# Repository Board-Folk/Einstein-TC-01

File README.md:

# Einstein TC-01

Repository for the 2025 Board Folk recreation of the main board of the Einstein TC-01 computer from Tatung.

This repository contains the Bill-of-Materials (iBOM), Gerbers and Kicad files for a remake of the Tatung Einstein TC-01 main board.

Projects are in Kicad 9.

## Revisions

* Version 1.1 Initial Public Release

## Modifications

* The 3 digit references have been abridged so they work in Kicad
* The factory modifications (cuts and bodge wires) for the reset circuit have been included on the board
* Bodge capacitor C70 included on board for printer port strobe delay
* A solder jumper next to socket M16 provides the common modification of 5V power to pin 6 on the video output socket as you'd have on a BBC Micro
* Some small silkscreen improvements have been made to avoid confusion

## Build Notes

* Power connectors are 5.08mm pin headers
* M6 keyboard pin header is 2.5mm not 2.54mm pitch
* Corner line indicator on transistor footprints signifies flat front side direction, NOT pin 1
* BC307 can be subtituted for BC557
* BC308 can be subtituted for BC558
* Reset switch is the same as the one found on the TRS-80 Model I
* The ADC0844 alternative footprint is a µPD7002 which requires C13 populating with 33nF (untested)
* The value/range of L101 "Chrominance Rejector" is at this time unknown

## Archive

Currently contains the original copy of the v1.1 main board, which hasn't changed. The updated main Kicad folder now contains additional symbols and footprints only.

## Credit

Mainboard PCB layout by Rob Taylor @peepouk. Schematics recreated by Ian Cudlip @grandoldian.

## Expansions

### TMSAdapterTC01

Adapter board to allow the use of a TMS9929 chip on the Tatung Einstein TC-01.

### EinsteinTC01PS2

Arduino Nano based PS/2 Keyboard Adapter for the TC-01.

### EinsteinTC01PS2Mini

ATMEGA328 based PS/2 Keyboard Adapter for the TC-01.

### V9958AdapterTC01

Yamaha V9958/V9938 Adapter with 192K Video RAM for the TC-01.

### TC02Mini

Simple non-replica remake of the TC-02 80 column adapter for the TC01.

### Joystick Adapters

#### TC01AtariJoystick

Dual Atari Digital Joystick Adapter.

#### Withdrawn Tandy Joystick Adapter

It turns out the y axis on Tandy joysticks is connected the other way round, which means it will require circuitry to make it work for Einstein games. Trying to think of something clever for that.

## Remixes

### Einstein CE

Simplified Einstein with bits removed to fit on a small board. See description in folder.

## Coming Soon

* Another, comprehensive remix with expansions

## Links

   [10.6875MHz HC-49U Crystal](https://slawmir.com.pl/rezonator-10-6875mhz-hc49u-x5-p-6105.html)  
   [5 pin "Domino" DIN Socket for Serial Port](https://vintage.imitation.parts/products/bbc-micro-parts/din-5-pcb-socket)  
   [Modifyable bracket for holding standard Volume Pot](https://sonicsynths.com/products/pcb_mounting_bracket_for_16mm_commercial_grade_pots)

## Thanks

  * The rest of the Board Folk Team

## Legal

As the product of this project is a replica of a proprietary product, the the author makes no claim of copyright to the schematics nor PCB layouts and releases these into the public domain, solely for the purposes of study and historical preservation.

You are free to produce PCBs based on this project's designs at your own risk and without limitation, for your own use or for sale and/or repair at a reasonable price. Attribution is appreciated. The authors are not obliged to provide support of any kind. 

Under no circumstances will the authors be held responsible or liable in any way for losses, damages or costs resulting from the use of the information and/or resources of this project. 

The resources are provided "as-is" without warranty of any kind, either expressed or implied, including, but not limited to, the implied warranties of merchantability and fitness for a particular purpose.

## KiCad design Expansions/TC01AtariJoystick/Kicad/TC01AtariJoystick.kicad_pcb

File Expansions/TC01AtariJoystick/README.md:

# Einstein TC01 Dual Atari Digital Joystick Adapter v1.1

Dual joystick adapter for Atari and compatible (Kempston/C64/Amiga/ST etc) digital joysticks. Tested with SVI Quickshot II Plus.

Based on Wizard Development 'BBC' joystick interface. Very clever, many thanks.

Update: Turns out having a fixed resistor at R1 was a bad idea as the output of the Vref circuit seems to be different between main board builds. This makes the analogue centre different. You can patch in a variable resistor/pot as an adjustment. One board needed changing to ~1K. Will post an update soon and some BASIC code for adjustment/tweaking.

## Versions

v1.1 Fix for x direction

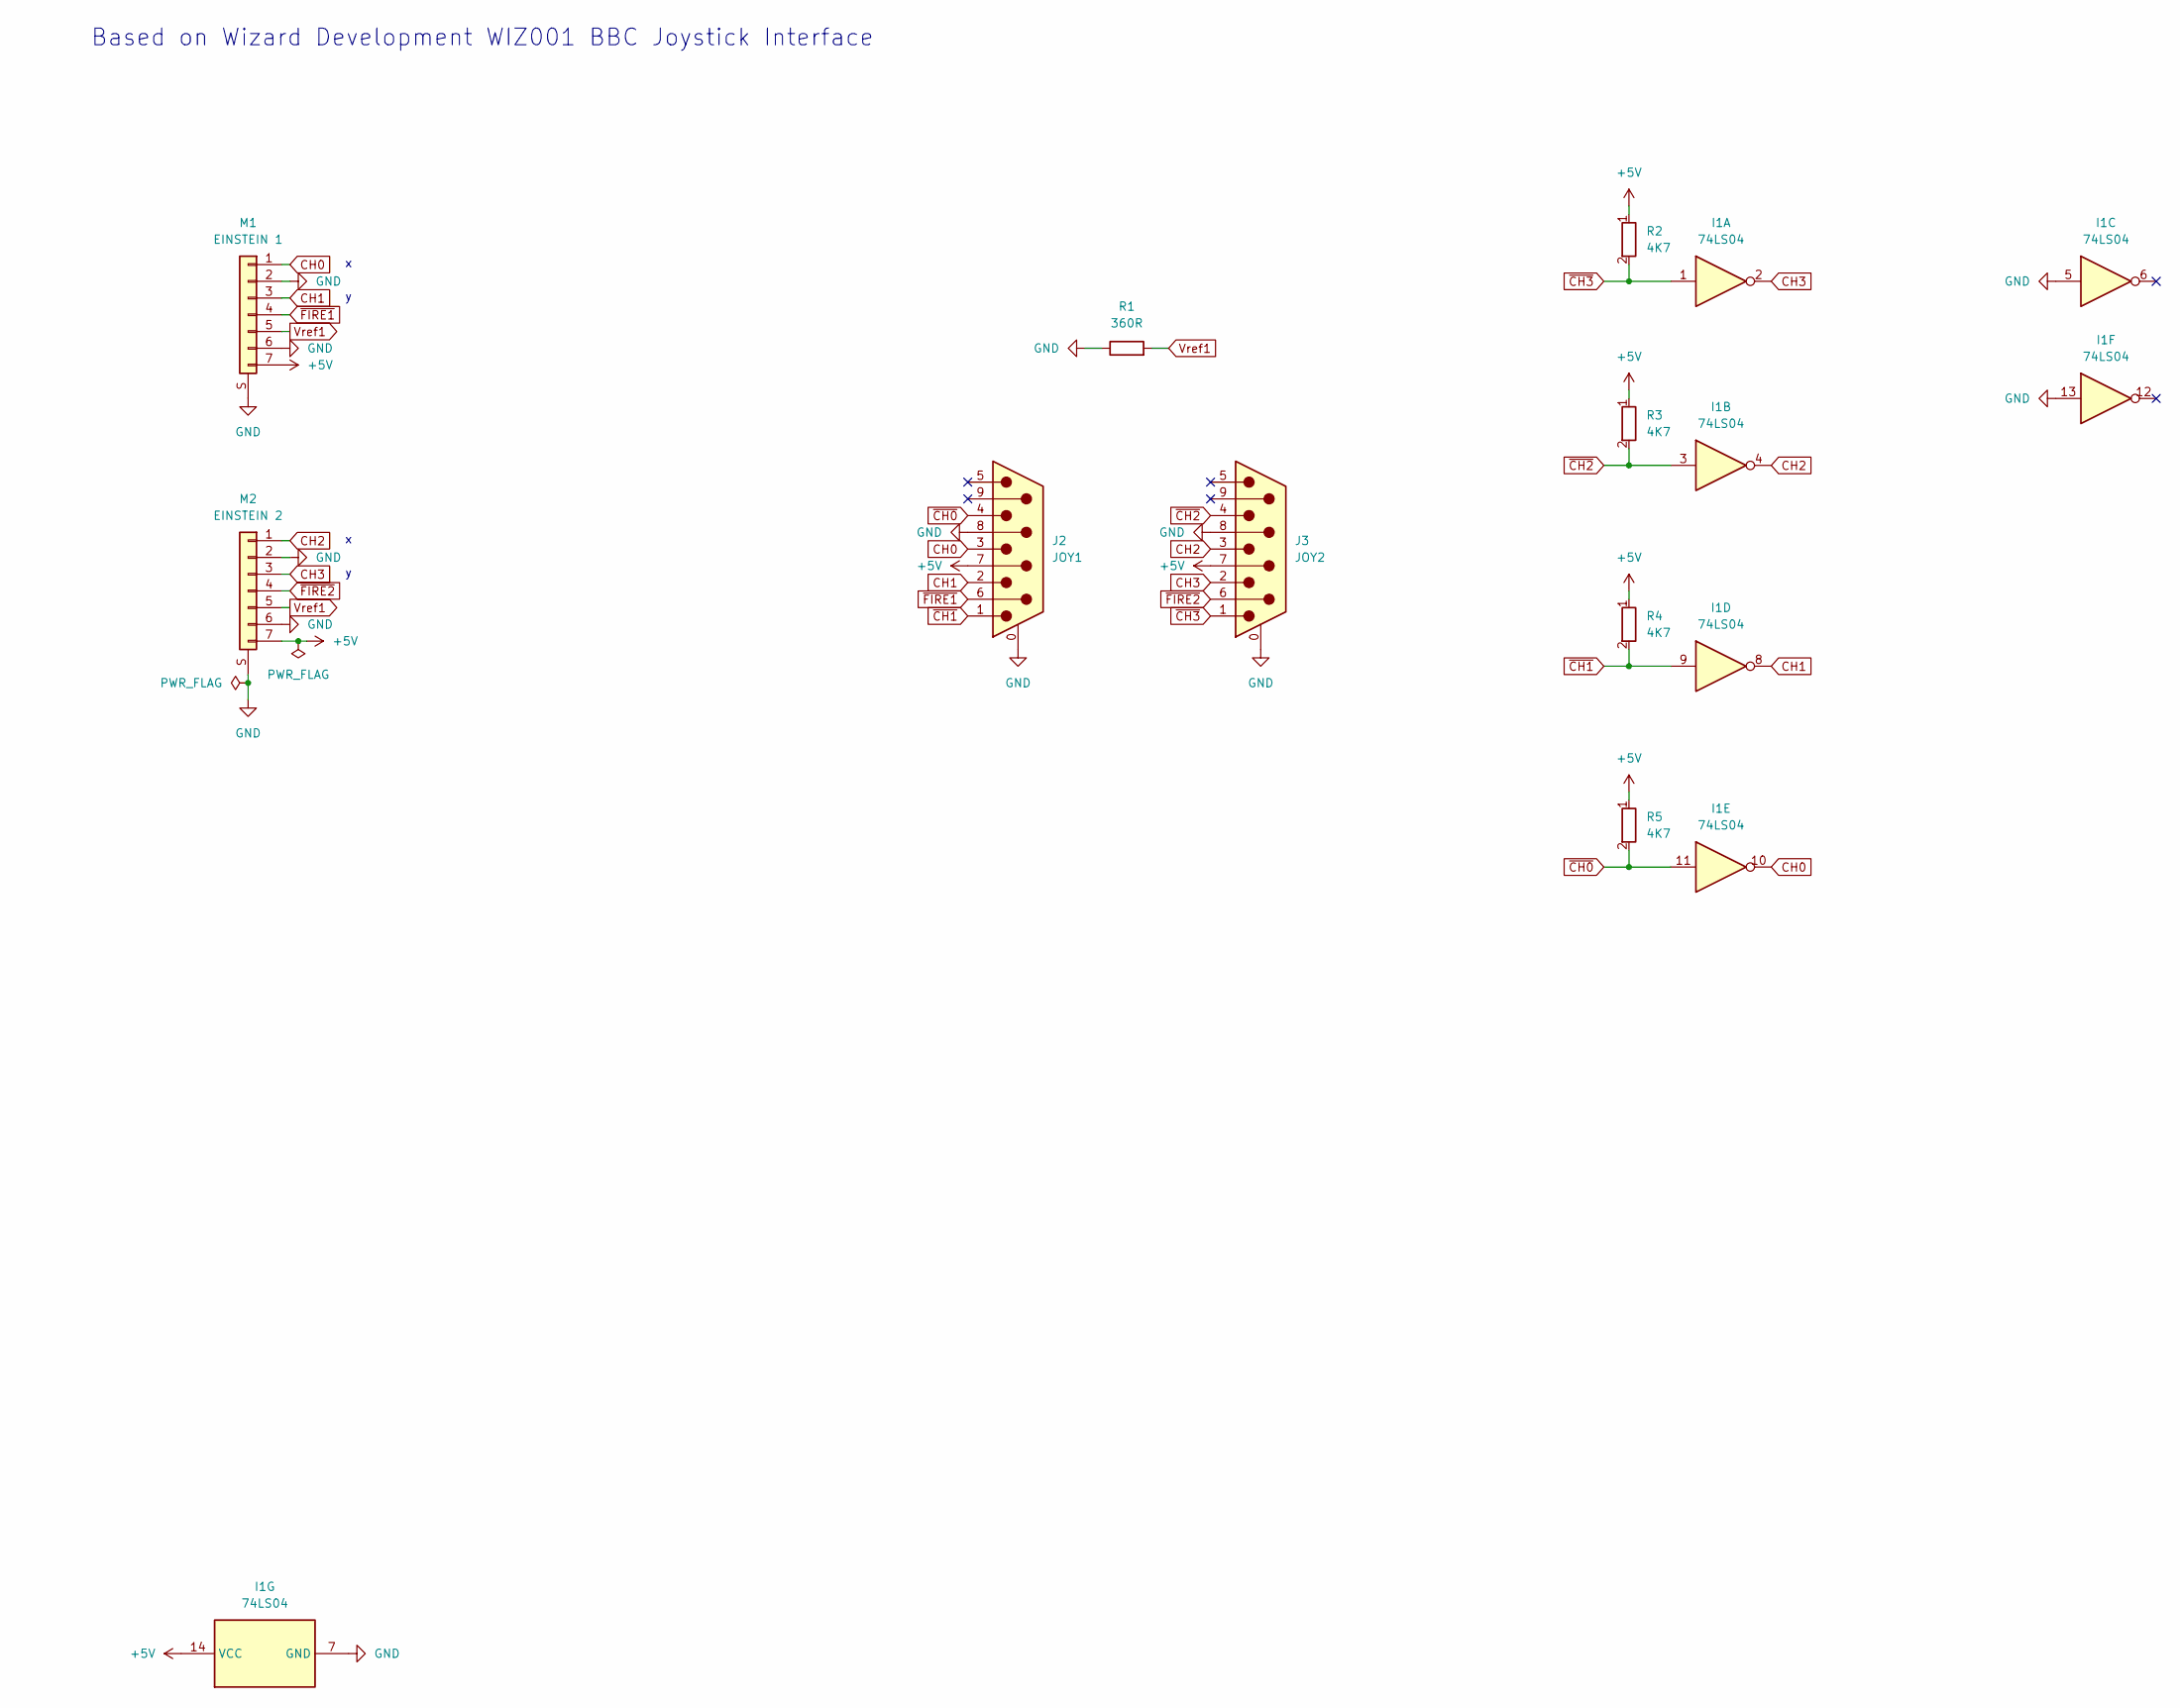
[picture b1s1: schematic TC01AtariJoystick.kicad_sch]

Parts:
I1: 74LS04; DIP-14_W7.62mm
J2: JOY1; DSUB-9_Pins_7.70mm_9.12mm
J3: JOY2; DSUB-9_Pins_7.70mm_9.12mm
M1: EINSTEIN 1; DIN7_3WAYS
M2: EINSTEIN 2; DIN7_3WAYS
R1: 360R; Resistor 10.16mm
R2, R3, R4, R5: 4K7; Resistor 10.16mm

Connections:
+5V: I1.14 (VCC), J2.7, J3.7, M1.7, M2.7, R2.1, R3.1, R4.1, R5.1
CH0: I1.10, J2.3, M1.1
CH1: I1.8, J2.2, M1.3
CH2: I1.4, J3.3, M2.1
CH3: I1.2, J3.2, M2.3
GND: I1.5, I1.7 (GND), I1.13, J2.0 (PAD), J2.8, J3.0 (PAD), J3.8, M1.2, M1.6, M1.S (Shield), M2.2, M2.6, M2.S (Shield), R1.1
Vref1: M1.5, M2.5, R1.2
~CH0: I1.11, J2.4, R5.2
~CH1: I1.9, J2.1, R4.2
~CH2: I1.3, J3.4, R3.2
~CH3: I1.1, J3.1, R2.2
~FIRE1: J2.6, M1.4
~FIRE2: J3.6, M2.4

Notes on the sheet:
Based on Wizard Development WIZ001 BBC Joystick Interface

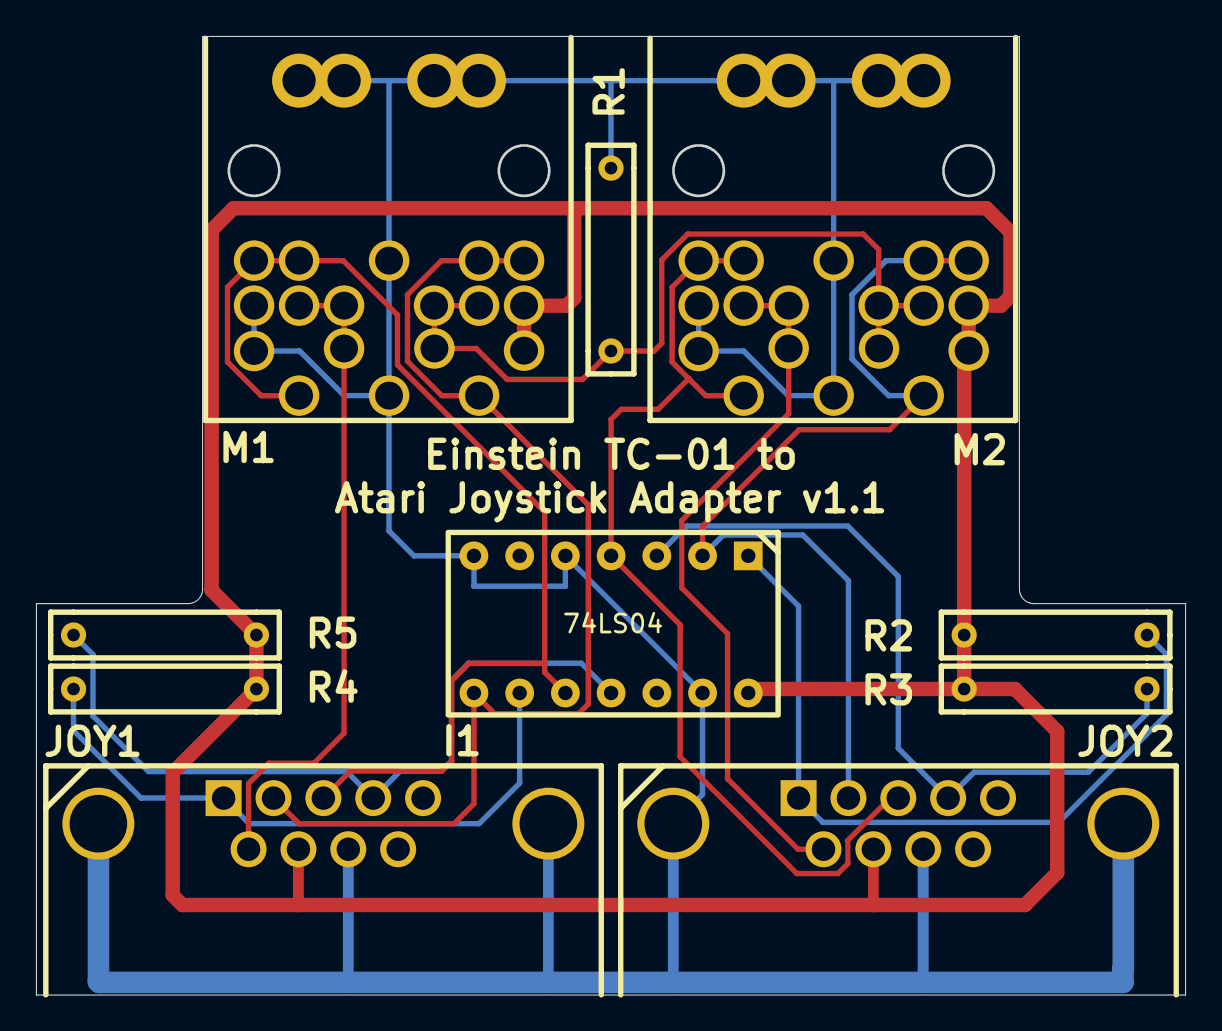
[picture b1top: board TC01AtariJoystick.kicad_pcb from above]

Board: 2 copper layers, 63.7 x 53.2 mm, 10 parts (0 on the bottom side), 13 nets.

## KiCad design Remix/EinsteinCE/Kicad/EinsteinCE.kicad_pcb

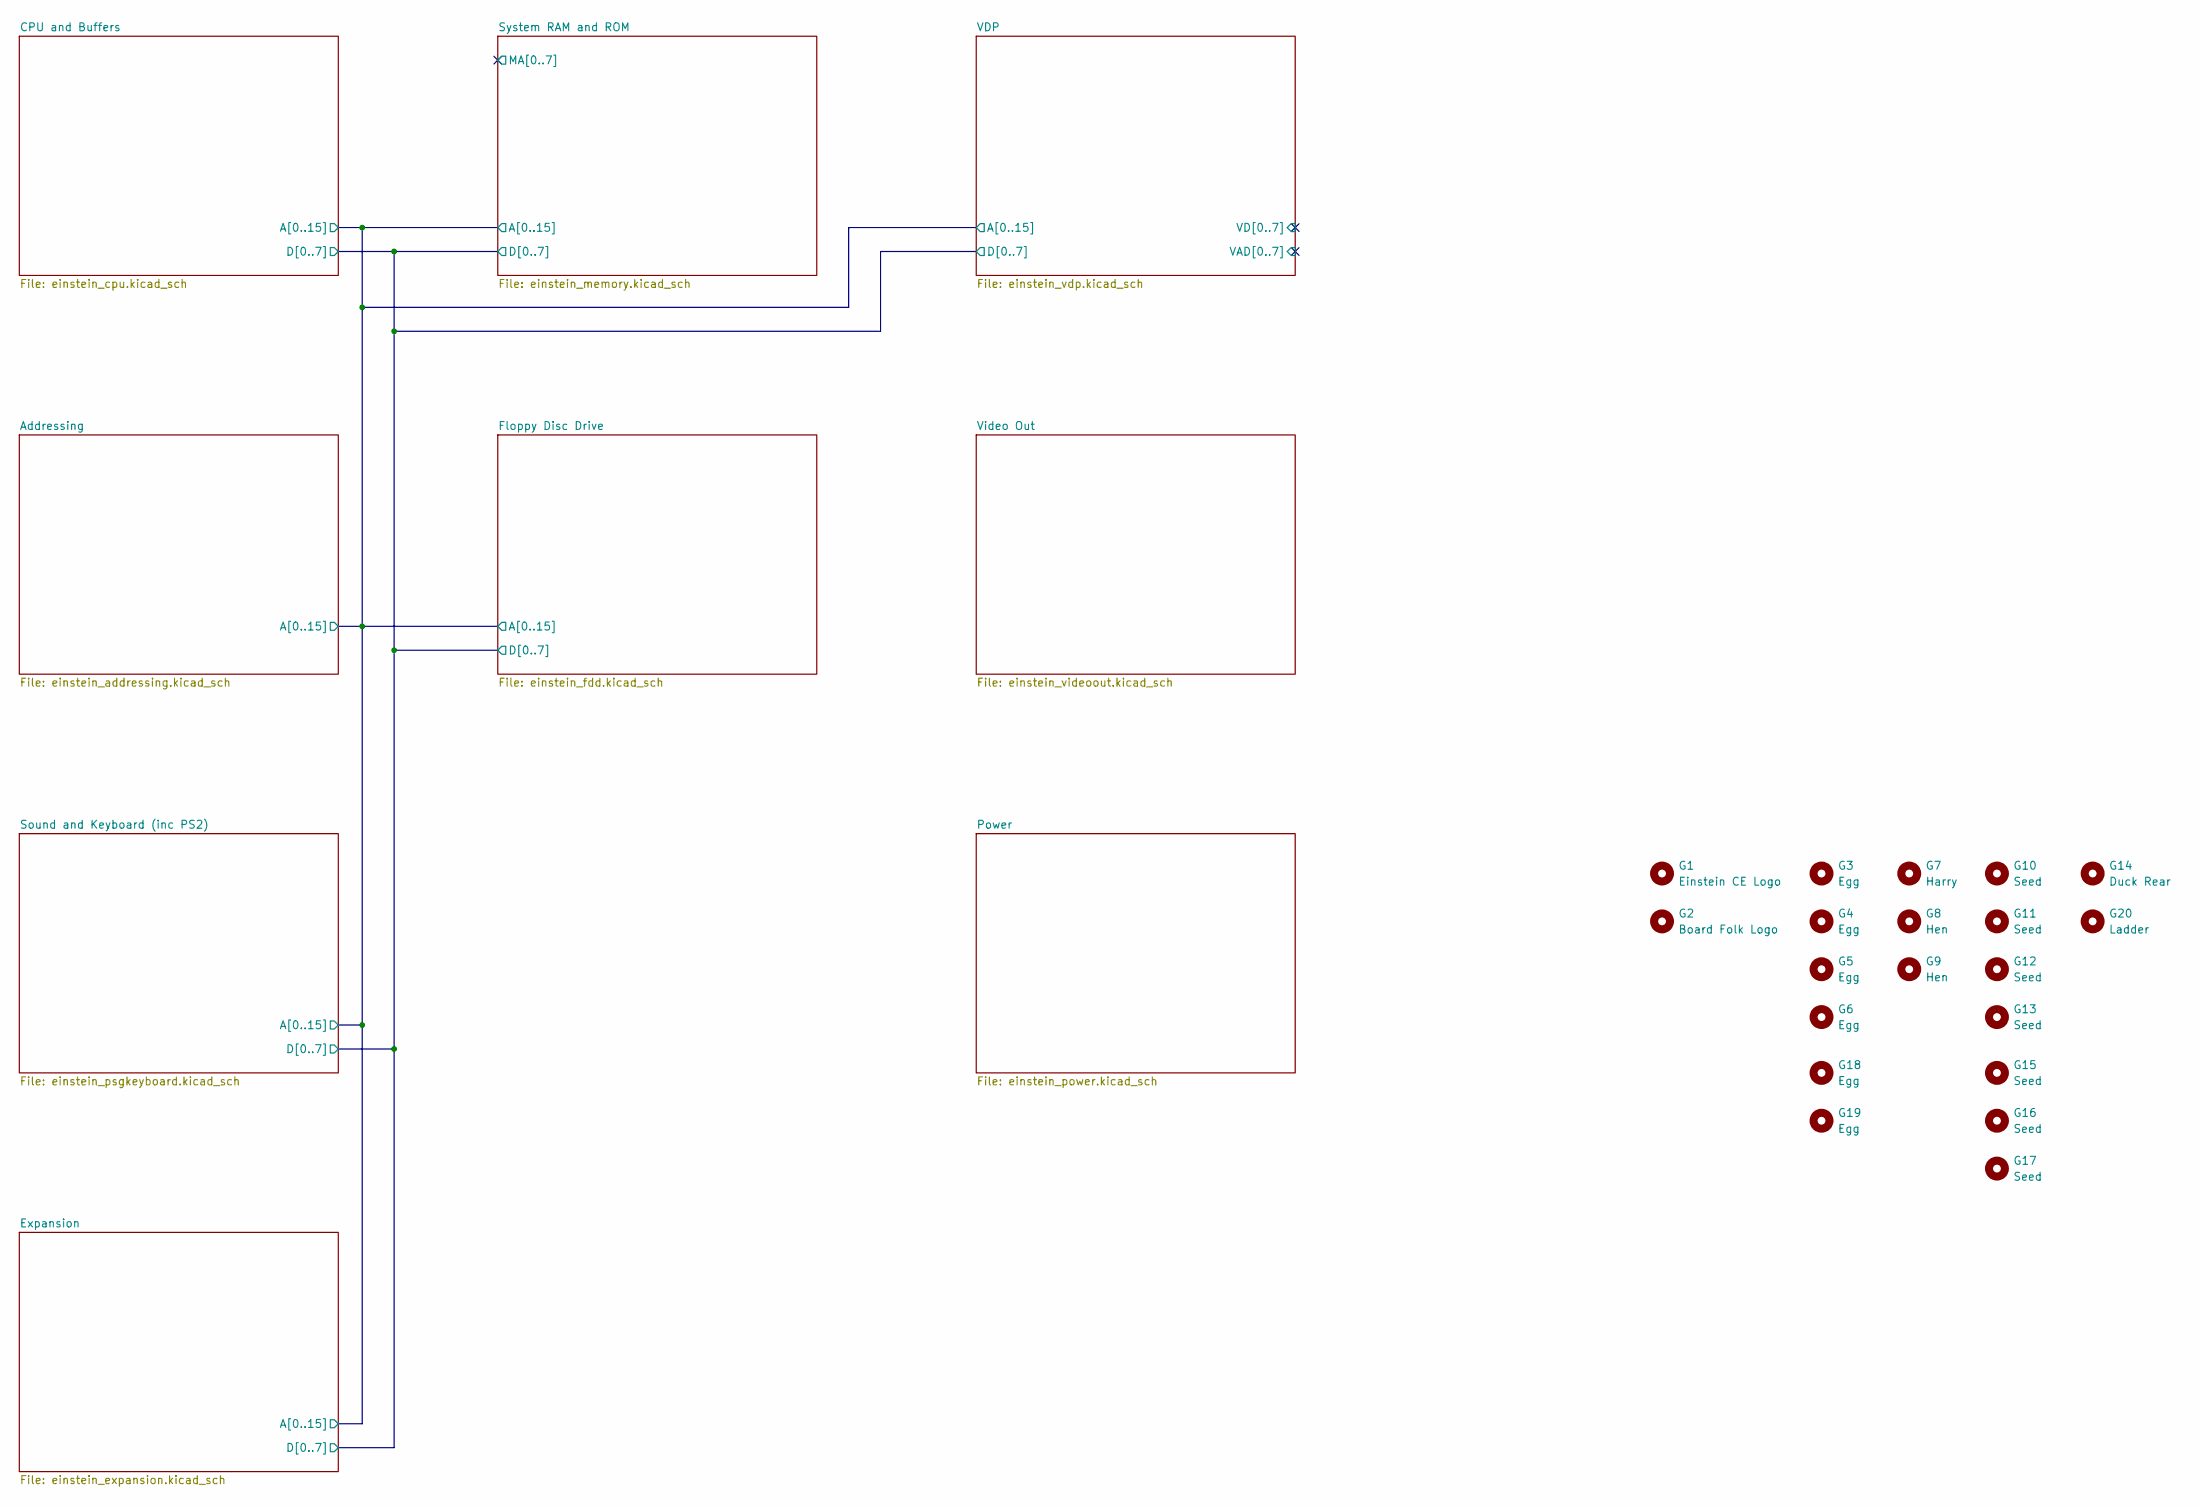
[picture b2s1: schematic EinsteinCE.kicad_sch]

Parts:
G1: Einstein CE Logo; EinsteinCELogo28mm
G2: Board Folk Logo; BF8
G3, G4, G5, G6, G18, G19: Egg; Egg5mm
G7: Harry; Harry8mm
G8: Hen; Hen8mm
G9: Hen; Hen_Left_8mm
G10, G11, G12, G13, G15, G16, G17: Seed; Seed6mm
G14: Duck Rear; Duck166mm
G20: Ladder

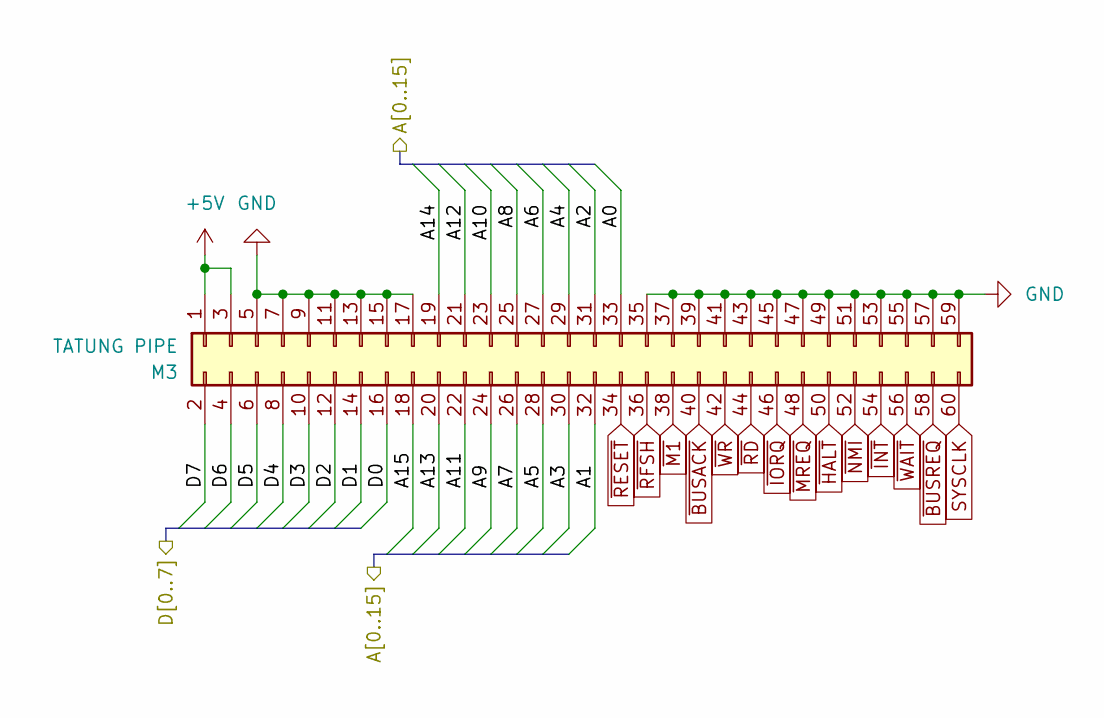
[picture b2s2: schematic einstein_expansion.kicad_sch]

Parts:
M3: TATUNG PIPE; M3 PinHeader_2x30_P2.54mm

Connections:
+5V: M3.1, M3.3; also elsewhere on the board
/Addressing/A0: M3.33; also elsewhere on the board
/Addressing/A1: M3.32; also elsewhere on the board
/Addressing/A2: M3.31; also elsewhere on the board
/Addressing/A3: M3.30; also elsewhere on the board
/Addressing/A4: M3.29; also elsewhere on the board
/Addressing/A5: M3.28; also elsewhere on the board
/Addressing/A6: M3.27; also elsewhere on the board
/Addressing/A7: M3.26; also elsewhere on the board
/Addressing/A8: M3.25; also elsewhere on the board
/Addressing/A9: M3.24; also elsewhere on the board
/Addressing/A10: M3.23; also elsewhere on the board
/Addressing/A11: M3.22; also elsewhere on the board
/Addressing/A12: M3.21; also elsewhere on the board
/Addressing/A13: M3.20; also elsewhere on the board
/Addressing/A14: M3.19; also elsewhere on the board
/Addressing/A15: M3.18; also elsewhere on the board
/CPU and Buffers/D0: M3.16; also elsewhere on the board
/CPU and Buffers/D1: M3.14; also elsewhere on the board
/CPU and Buffers/D2: M3.12; also elsewhere on the board
/CPU and Buffers/D3: M3.10; also elsewhere on the board
/CPU and Buffers/D4: M3.8; also elsewhere on the board
/CPU and Buffers/D5: M3.6; also elsewhere on the board
/CPU and Buffers/D6: M3.4; also elsewhere on the board
/CPU and Buffers/D7: M3.2; also elsewhere on the board
GND: M3.5, M3.7, M3.9, M3.11, M3.13, M3.15, M3.17, M3.35, M3.37, M3.39, M3.41, M3.43, M3.45, M3.47, M3.49, M3.51, M3.53, M3.55, M3.57, M3.59; also elsewhere on the board
SYSCLK: M3.60; also elsewhere on the board
~BUSACK: M3.40; also elsewhere on the board
~BUSREQ: M3.58; also elsewhere on the board
~HALT: M3.50; also elsewhere on the board
~INT: M3.54; also elsewhere on the board
~IORQ: M3.46; also elsewhere on the board
~M1: M3.38; also elsewhere on the board
~MREQ: M3.48; also elsewhere on the board
~NMI: M3.52; also elsewhere on the board
~RD: M3.44; also elsewhere on the board
~RESET: M3.34; also elsewhere on the board
~RFSH: M3.36; also elsewhere on the board
~WAIT: M3.56; also elsewhere on the board
~WR: M3.42; also elsewhere on the board

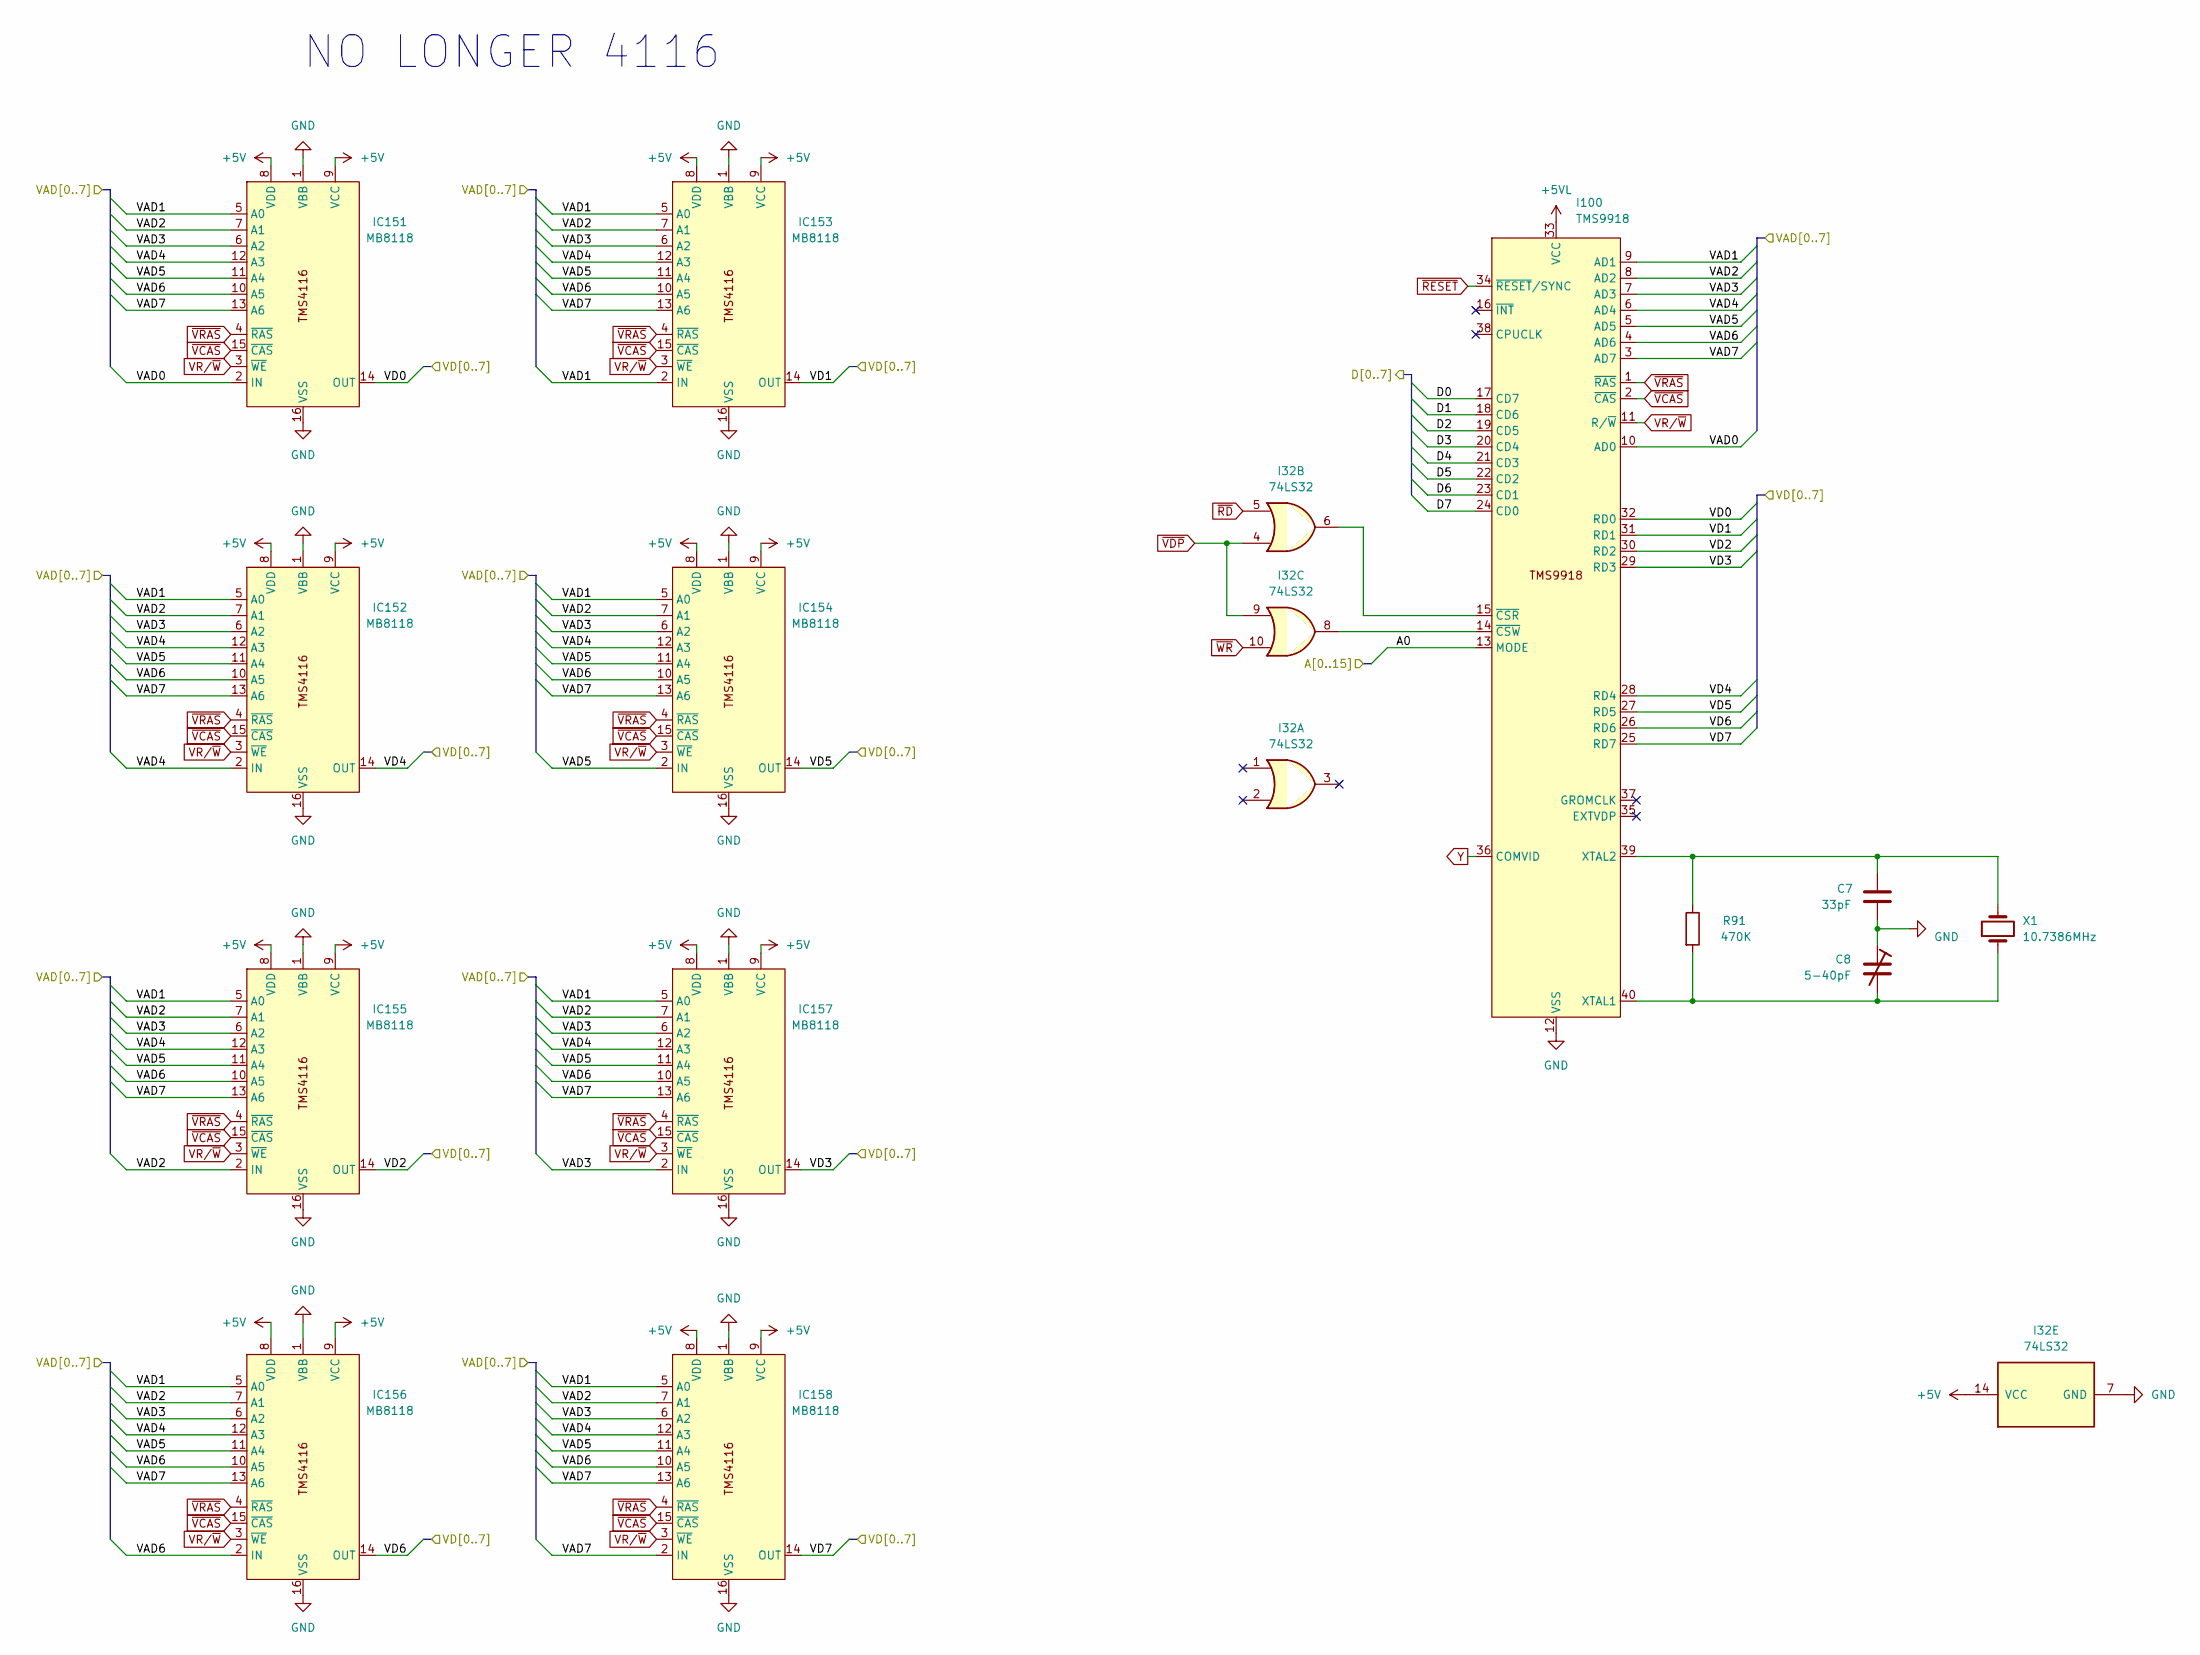
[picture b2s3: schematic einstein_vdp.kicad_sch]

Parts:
C7: 33pF; C_Disc_2.54mm
C8: 5-40pF; CVN6500
I32: 74LS32; DIP-14_W7.62mm
I100: TMS9918; DIP-40_W15.24mm
IC151, IC152, IC153, IC154, IC155, IC156, IC157, IC158: MB8118; DIP-16_W7.62mm
R91: 470K; Resistor 10.16mm
X1: 10.7386MHz; Crystal

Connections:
+5V: I32.14 (VCC), IC151.8 (VDD), IC151.9 (VCC), IC152.8 (VDD), IC152.9 (VCC), IC153.8 (VDD), IC153.9 (VCC), IC154.8 (VDD), IC154.9 (VCC), IC155.8 (VDD), IC155.9 (VCC), IC156.8 (VDD), IC156.9 (VCC), IC157.8 (VDD), IC157.9 (VCC), IC158.8 (VDD), IC158.9 (VCC); also elsewhere on the board
+5VL: I100.33 (VCC); also elsewhere on the board
/Addressing/A0: I100.13 (MODE); also elsewhere on the board
/CPU and Buffers/D0: I100.17 (CD7); also elsewhere on the board
/CPU and Buffers/D1: I100.18 (CD6); also elsewhere on the board
/CPU and Buffers/D2: I100.19 (CD5); also elsewhere on the board
/CPU and Buffers/D3: I100.20 (CD4); also elsewhere on the board
/CPU and Buffers/D4: I100.21 (CD3); also elsewhere on the board
/CPU and Buffers/D5: I100.22 (CD2); also elsewhere on the board
/CPU and Buffers/D6: I100.23 (CD1); also elsewhere on the board
/CPU and Buffers/D7: I100.24 (CD0); also elsewhere on the board
/VDP/VAD0: I100.10 (AD0), IC151.2 (IN)
/VDP/VAD1: I100.9 (AD1), IC151.5 (A0), IC152.5 (A0), IC153.2 (IN), IC153.5 (A0), IC154.5 (A0), IC155.5 (A0), IC156.5 (A0), IC157.5 (A0), IC158.5 (A0)
/VDP/VAD2: I100.8 (AD2), IC151.7 (A1), IC152.7 (A1), IC153.7 (A1), IC154.7 (A1), IC155.2 (IN), IC155.7 (A1), IC156.7 (A1), IC157.7 (A1), IC158.7 (A1)
/VDP/VAD3: I100.7 (AD3), IC151.6 (A2), IC152.6 (A2), IC153.6 (A2), IC154.6 (A2), IC155.6 (A2), IC156.6 (A2), IC157.2 (IN), IC157.6 (A2), IC158.6 (A2)
/VDP/VAD4: I100.6 (AD4), IC151.12 (A3), IC152.2 (IN), IC152.12 (A3), IC153.12 (A3), IC154.12 (A3), IC155.12 (A3), IC156.12 (A3), IC157.12 (A3), IC158.12 (A3)
/VDP/VAD5: I100.5 (AD5), IC151.11 (A4), IC152.11 (A4), IC153.11 (A4), IC154.2 (IN), IC154.11 (A4), IC155.11 (A4), IC156.11 (A4), IC157.11 (A4), IC158.11 (A4)
/VDP/VAD6: I100.4 (AD6), IC151.10 (A5), IC152.10 (A5), IC153.10 (A5), IC154.10 (A5), IC155.10 (A5), IC156.2 (IN), IC156.10 (A5), IC157.10 (A5), IC158.10 (A5)
/VDP/VAD7: I100.3 (AD7), IC151.13 (A6), IC152.13 (A6), IC153.13 (A6), IC154.13 (A6), IC155.13 (A6), IC156.13 (A6), IC157.13 (A6), IC158.2 (IN), IC158.13 (A6)
/VDP/VD0: I100.32 (RD0), IC151.14 (OUT)
/VDP/VD1: I100.31 (RD1), IC153.14 (OUT)
/VDP/VD2: I100.30 (RD2), IC155.14 (OUT)
/VDP/VD3: I100.29 (RD3), IC157.14 (OUT)
/VDP/VD4: I100.28 (RD4), IC152.14 (OUT)
/VDP/VD5: I100.27 (RD5), IC154.14 (OUT)
/VDP/VD6: I100.26 (RD6), IC156.14 (OUT)
/VDP/VD7: I100.25 (RD7), IC158.14 (OUT)
GND: C7.2, C8.1, I32.7 (GND), I100.12 (VSS), IC151.1 (VBB), IC151.16 (VSS), IC152.1 (VBB), IC152.16 (VSS), IC153.1 (VBB), IC153.16 (VSS), IC154.1 (VBB), IC154.16 (VSS), IC155.1 (VBB), IC155.16 (VSS), IC156.1 (VBB), IC156.16 (VSS), IC157.1 (VBB), IC157.16 (VSS), IC158.1 (VBB), IC158.16 (VSS); also elsewhere on the board
unnamed: C8.2, I100.40 (XTAL1), R91.2, X1.1
unnamed: C7.1, I100.39 (XTAL2), R91.1, X1.2
unnamed: I32.6, I100.15 (~CSR)
unnamed: I32.8, I100.14 (~CSW)
VR/~W: I100.11 (R/~W), IC151.3 (~WE), IC152.3 (~WE), IC153.3 (~WE), IC154.3 (~WE), IC155.3 (~WE), IC156.3 (~WE), IC157.3 (~WE), IC158.3 (~WE)
Y: I100.36 (COMVID); also elsewhere on the board
~RD: I32.5; also elsewhere on the board
~RESET: I100.34 (~RESET/SYNC); also elsewhere on the board
~VCAS: I100.2 (~CAS), IC151.15 (~CAS), IC152.15 (~CAS), IC153.15 (~CAS), IC154.15 (~CAS), IC155.15 (~CAS), IC156.15 (~CAS), IC157.15 (~CAS), IC158.15 (~CAS)
~VDP: I32.4, I32.9; also elsewhere on the board
~VRAS: I100.1 (~RAS), IC151.4 (~RAS), IC152.4 (~RAS), IC153.4 (~RAS), IC154.4 (~RAS), IC155.4 (~RAS), IC156.4 (~RAS), IC157.4 (~RAS), IC158.4 (~RAS)
~WR: I32.10; also elsewhere on the board

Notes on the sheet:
NO LONGER 4116
